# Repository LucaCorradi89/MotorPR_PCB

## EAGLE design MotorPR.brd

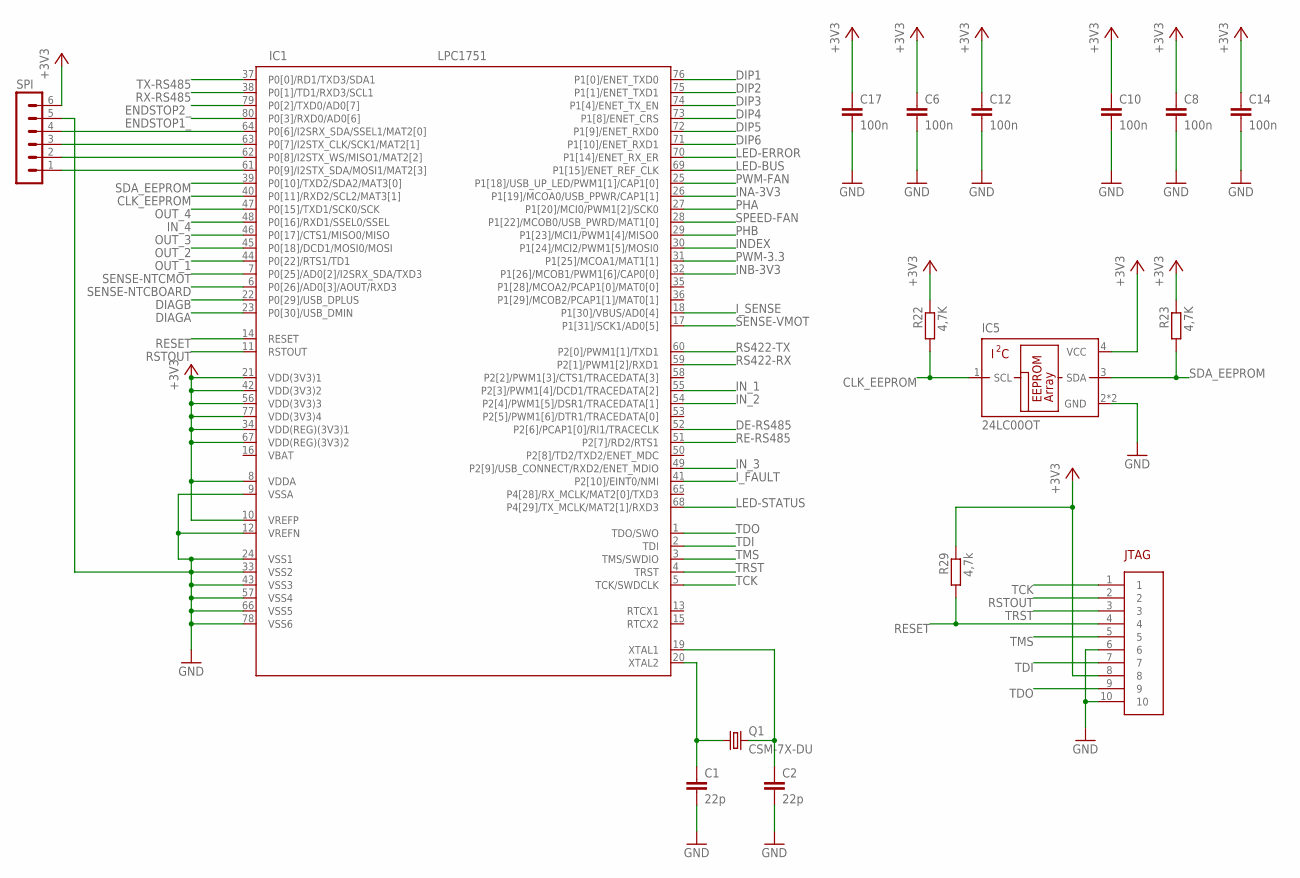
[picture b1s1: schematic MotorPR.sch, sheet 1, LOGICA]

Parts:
C1, C2: 22p; C0805
C6, C8, C10, C12, C14, C17: 100n; C0805
IC1: LPC1751; LQFP80-12X12
IC5: 24LC00OT; SOT23-5L
JTAG: MOLEX-52808-1070
Q1: CSM-7X-DU
R22, R23: 4,7K; R0805W
R29: 4,7k; R0805W
SPI: MA06-1

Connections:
+3V3: C6.1, C8.1, C10.1, C12.1, C14.1, C17.1, IC1.8 (VDDA), IC1.10 (VREFP), IC1.21 (VDD(3V3)1), IC1.34 (VDD(REG)(3V3)1), IC1.42 (VDD(3V3)2), IC1.56 (VDD(3V3)3), IC1.67 (VDD(REG)(3V3)2), IC1.77 (VDD(3V3)4), IC5.4 (VCC), JTAG.8, R22.1, R23.1, R29.1, SPI.6; also elsewhere on the board
CLK_EEPROM: IC1.40 (P0[11]/RXD2/SCL2/MAT3[1]), IC5.1 (SCL), R22.2
DE-RS485: IC1.52 (P2[6]/PCAP1[0]/RI1/TRACECLK); also elsewhere on the board
DIAGA: IC1.23 (P0[30]/USB_DMIN); also elsewhere on the board
DIAGB: IC1.22 (P0[29]/USB_DPLUS); also elsewhere on the board
DIP1: IC1.76 (P1[0]/ENET_TXD0); also elsewhere on the board
DIP2: IC1.75 (P1[1]/ENET_TXD1); also elsewhere on the board
DIP3: IC1.74 (P1[4]/ENET_TX_EN); also elsewhere on the board
DIP4: IC1.73 (P1[8]/ENET_CRS); also elsewhere on the board
DIP5: IC1.72 (P1[9]/ENET_RXD0); also elsewhere on the board
DIP6: IC1.71 (P1[10]/ENET_RXD1); also elsewhere on the board
ENDSTOP1_: IC1.80 (P0[3]/RXD0/AD0[6]); also elsewhere on the board
ENDSTOP2_: IC1.79 (P0[2]/TXD0/AD0[7]); also elsewhere on the board
GND: C1.2, C2.2, C6.2, C8.2, C10.2, C12.2, C14.2, C17.2, IC1.9 (VSSA), IC1.12 (VREFN), IC1.24 (VSS1), IC1.33 (VSS2), IC1.43 (VSS3), IC1.57 (VSS4), IC1.66 (VSS5), IC1.78 (VSS6), IC5.2 (GND), IC5.5 (GND), JTAG.6, JTAG.10, SPI.5; also elsewhere on the board
INA-3V3: IC1.26 (P1[19]/MCOA0/USB_PPWR/CAP1[1]); also elsewhere on the board
INB-3V3: IC1.32 (P1[26]/MCOB1/PWM1[6]/CAP0[0]); also elsewhere on the board
INDEX: IC1.30 (P1[24]/MCI2/PWM1[5]/MOSI0); also elsewhere on the board
IN_1: IC1.55 (P2[3]/PWM1[4]/DCD1/TRACEDATA[2]); also elsewhere on the board
IN_2: IC1.54 (P2[4]/PWM1[5]/DSR1/TRACEDATA[1]); also elsewhere on the board
IN_3: IC1.49 (P2[9]/USB_CONNECT/RXD2/ENET_MDIO); also elsewhere on the board
IN_4: IC1.48 (P0[16]/RXD1/SSEL0/SSEL); also elsewhere on the board
I_FAULT: IC1.41 (P2[10]/EINT0/NMI); also elsewhere on the board
I_SENSE: IC1.18 (P1[30]/VBUS/AD0[4]); also elsewhere on the board
LED-BUS: IC1.69 (P1[15]/ENET_REF_CLK); also elsewhere on the board
LED-ERROR: IC1.70 (P1[14]/ENET_RX_ER); also elsewhere on the board
LED-STATUS: IC1.68 (P4[29]/TX_MCLK/MAT2[1]/RXD3); also elsewhere on the board
unnamed: C2.1, IC1.19 (XTAL1), Q1.2
unnamed: IC1.61 (P0[9]/I2STX_SDA/MOSI1/MAT2[3]), SPI.1
unnamed: C1.1, IC1.20 (XTAL2), Q1.1
unnamed: IC1.62 (P0[8]/I2STX_WS/MISO1/MAT2[2]), SPI.2
unnamed: IC1.63 (P0[7]/I2STX_CLK/SCK1/MAT2[1]), SPI.3
unnamed: IC1.64 (P0[6]/I2SRX_SDA/SSEL1/MAT2[0]), SPI.4
OUT_1: IC1.44 (P0[22]/RTS1/TD1); also elsewhere on the board
OUT_2: IC1.45 (P0[18]/DCD1/MOSI0/MOSI); also elsewhere on the board
OUT_3: IC1.46 (P0[17]/CTS1/MISO0/MISO); also elsewhere on the board
OUT_4: IC1.47 (P0[15]/TXD1/SCK0/SCK); also elsewhere on the board
PHA: IC1.27 (P1[20]/MCI0/PWM1[2]/SCK0); also elsewhere on the board
PHB: IC1.29 (P1[23]/MCI1/PWM1[4]/MISO0); also elsewhere on the board
PWM-3.3: IC1.31 (P1[25]/MCOA1/MAT1[1]); also elsewhere on the board
PWM-FAN: IC1.25 (P1[18]/USB_UP_LED/PWM1[1]/CAP1[0]); also elsewhere on the board
RE-RS485: IC1.51 (P2[7]/RD2/RTS1); also elsewhere on the board
RESET: IC1.14 (RESET), JTAG.4, R29.2
RS422-RX: IC1.59 (P2[1]/PWM1[2]/RXD1); also elsewhere on the board
RS422-TX: IC1.60 (P2[0]/PWM1[1]/TXD1); also elsewhere on the board
RSTOUT: IC1.11 (RSTOUT), JTAG.2
RX-RS485: IC1.38 (P0[1]/TD1/RXD3/SCL1); also elsewhere on the board
SDA_EEPROM: IC1.39 (P0[10]/TXD2/SDA2/MAT3[0]), IC5.3 (SDA), R23.2
SENSE-NTCBOARD: IC1.6 (P0[26]/AD0[3]/AOUT/RXD3); also elsewhere on the board
SENSE-NTCMOT: IC1.7 (P0[25]/AD0[2]/I2SRX_SDA/TXD3); also elsewhere on the board
SENSE-VMOT: IC1.17 (P1[31]/SCK1/AD0[5]); also elsewhere on the board
SPEED-FAN: IC1.28 (P1[22]/MCOB0/USB_PWRD/MAT1[0]); also elsewhere on the board
TCK: IC1.5 (TCK/SWDCLK), JTAG.1
TDI: IC1.2 (TDI), JTAG.7
TDO: IC1.1 (TDO/SWO), JTAG.9
TMS: IC1.3 (TMS/SWDIO), JTAG.5
TRST: IC1.4 (TRST), JTAG.3
TX-RS485: IC1.37 (P0[0]/RD1/TXD3/SDA1); also elsewhere on the board
VBAT: IC1.16 (VBAT)

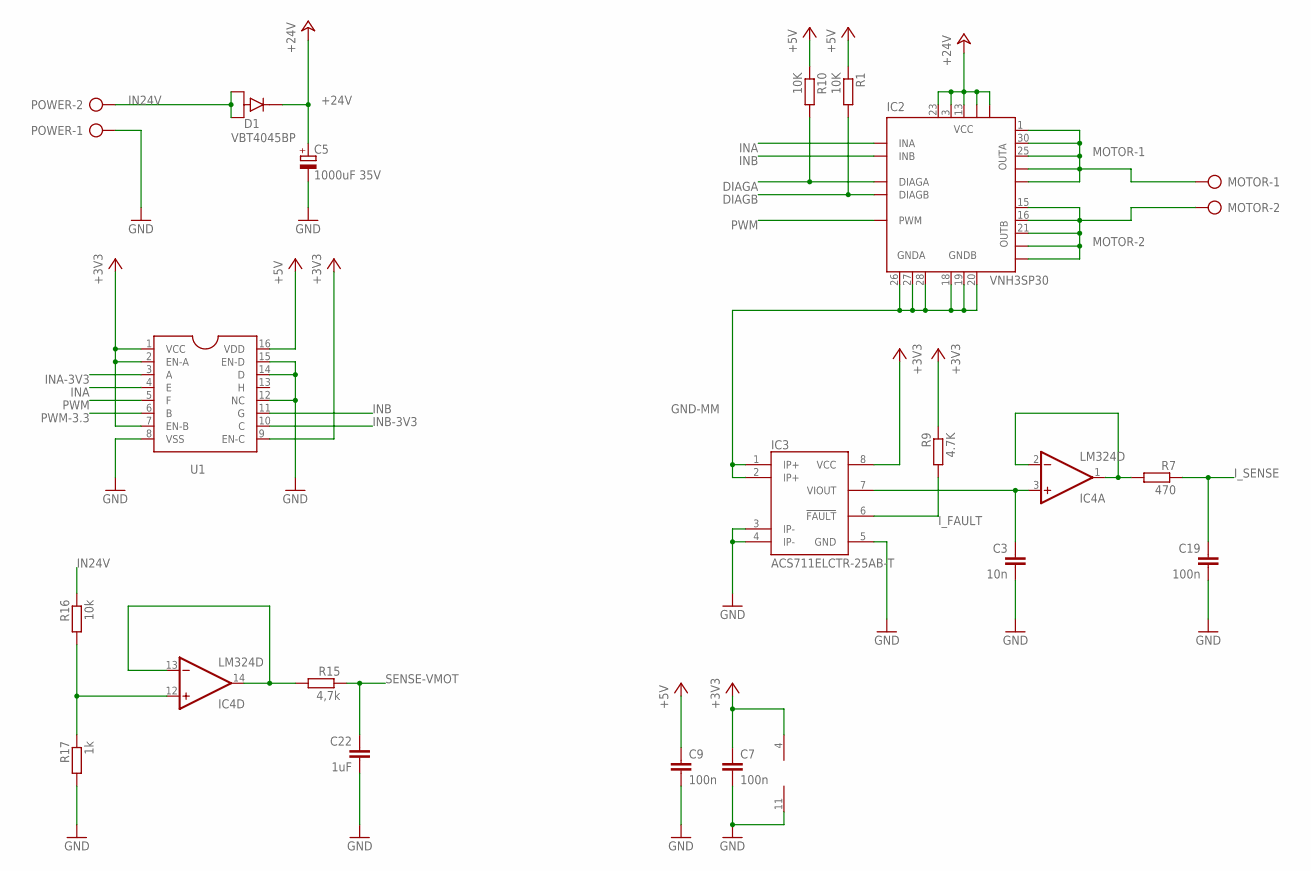
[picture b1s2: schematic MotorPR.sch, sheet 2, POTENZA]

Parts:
C3: 10n; C0805
C5: 1000uF 35V; E7,5-18
C7, C9, C19: 100n; C0805
C22: 1uF; C0805
D1: VBT4045BP; TO-263AB
IC2: VNH3SP30; MULTIPOWERSO-30
IC3: ACS711ELCTR-25AB-T; SO08
IC4: LM324D; SO14
MOTOR: AK300/2
POWER: AK300/2
R1, R10: 10K; R0805W
R7: 470; R0805W
R9: 4.7K; R0805W
R15: 4,7k; R0805W
R16: 10k; M1206
R17: 1k; M1206
U1: CD40109B; PW-PDSO-G16

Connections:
+3V3: C7.1, IC3.8 (VCC), IC4.4 (V+), R9.1, U1.1 (VCC), U1.2 (EN-A), U1.7 (EN-B), U1.9 (EN-C); also elsewhere on the board
+5V: C9.1, R1.1, R10.1, U1.16 (VDD); also elsewhere on the board
+24V: C5.+, D1.K, IC2.3 (VCC), IC2.13 (VCC), IC2.23 (VCC), IC2.VCC, IC2.VCC@1 (VCC)
DIAGA: IC2.6 (DIAGA), R10.2; also elsewhere on the board
DIAGB: IC2.10 (DIAGB), R1.2; also elsewhere on the board
GND: C3.2, C5.-, C7.2, C9.2, C19.2, C22.2, IC3.3 (IP-), IC3.4 (IP-), IC3.5 (GND), IC4.11 (V-), POWER.1, R17.2, U1.8 (VSS), U1.12 (NC), U1.14 (D), U1.15 (EN-D); also elsewhere on the board
GND-MM: IC2.18 (GNDB), IC2.19 (GNDB), IC2.20 (GNDB), IC2.26 (GNDA), IC2.27 (GNDA), IC2.28 (GNDA), IC3.1 (IP+), IC3.2 (IP+)
IN24V: D1.A1, D1.A2, POWER.2, R16.1; also elsewhere on the board
INA: IC2.5 (INA), U1.4 (E)
INA-3V3: U1.3 (A); also elsewhere on the board
INB: IC2.11 (INB), U1.11 (G)
INB-3V3: U1.10 (C); also elsewhere on the board
I_FAULT: IC3.6 (!FAULT!), R9.2; also elsewhere on the board
I_SENSE: C19.1, R7.1; also elsewhere on the board
MOTOR-1: IC2.1 (OUTA), IC2.25 (OUTA), IC2.30 (OUTA), IC2.OUTA, IC2.OUTA@1 (OUTA), MOTOR.1
MOTOR-2: IC2.15 (OUTB), IC2.16 (OUTB), IC2.21 (OUTB), IC2.OUTB, IC2.OUTB@1 (OUTB), MOTOR.2
unnamed: C3.1, IC3.7 (VIOUT), IC4.3 (+IN)
unnamed: IC4.13 (-IN), IC4.14 (OUT), R15.2
unnamed: IC4.1 (OUT), IC4.2 (-IN), R7.2
unnamed: IC4.12 (+IN), R16.2, R17.1
PWM: IC2.8 (PWM), U1.5 (F)
PWM-3.3: U1.6 (B); also elsewhere on the board
SENSE-VMOT: C22.1, R15.1; also elsewhere on the board

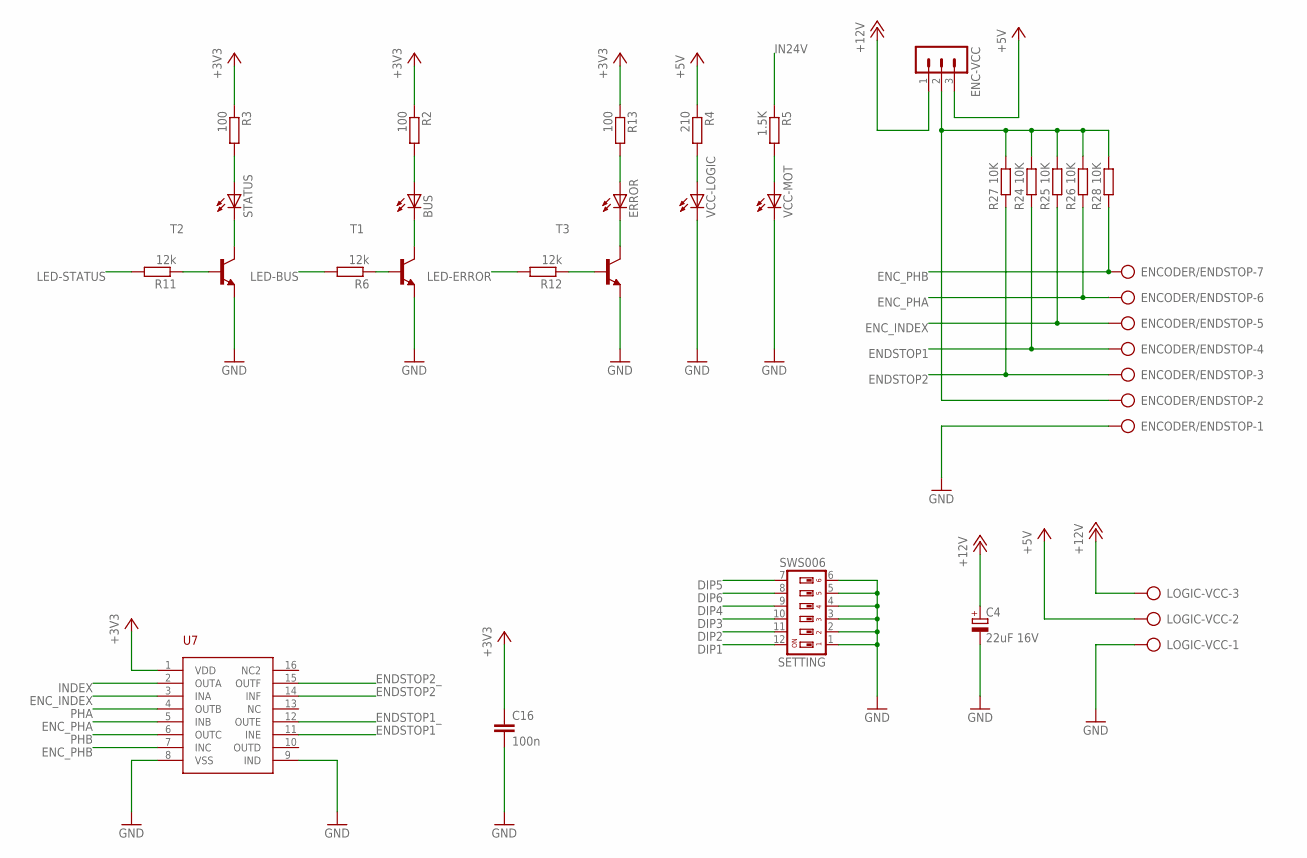
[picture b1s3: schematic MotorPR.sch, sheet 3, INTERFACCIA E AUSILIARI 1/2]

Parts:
BUS: LEDCHIPLED_1206; CHIPLED_1206
C4: 22uF 16V; 153CLV-0605
C16: 100n; C0805
ENC-VCC: MA03-1
ENCODER/ENDSTOP: AK300/7
ERROR: LEDCHIPLED_1206; CHIPLED_1206
LOGIC-VCC: AK300/3
R2, R3, R13: 100; R0805W
R4: 210; R0805W
R5: 1.5K; R0805W
R6, R11, R12: 12k; R0805W
R24, R25, R26, R27, R28: 10K; R0805W
SETTING: SWS006; DIP6-SMD
STATUS: LEDCHIPLED_1206; CHIPLED_1206
T1, T2, T3: BC808-NPN-SOT23-BEC; SOT23-BEC
U7: MC14050B; PDSO-G16
VCC-LOGIC: LEDCHIPLED_1206; CHIPLED_1206
VCC-MOT: LEDCHIPLED_1206; CHIPLED_1206

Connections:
+3V3: C16.1, R2.1, R3.1, R13.1, U7.1 (VDD); also elsewhere on the board
+5V: ENC-VCC.3, LOGIC-VCC.2, R4.1; also elsewhere on the board
+12V: C4.+, ENC-VCC.1, LOGIC-VCC.3; also elsewhere on the board
DIP1: SETTING.12; also elsewhere on the board
DIP2: SETTING.11; also elsewhere on the board
DIP3: SETTING.10; also elsewhere on the board
DIP4: SETTING.9; also elsewhere on the board
DIP5: SETTING.7; also elsewhere on the board
DIP6: SETTING.8; also elsewhere on the board
ENC_INDEX: ENCODER/ENDSTOP.5, R25.2, U7.3 (INA)
ENC_PHA: ENCODER/ENDSTOP.6, R26.2, U7.5 (INB)
ENC_PHB: ENCODER/ENDSTOP.7, R28.2, U7.7 (INC)
ENDSTOP1: ENCODER/ENDSTOP.4, R24.2, U7.11 (INE)
ENDSTOP1_: U7.12 (OUTE); also elsewhere on the board
ENDSTOP2: ENCODER/ENDSTOP.3, R27.2, U7.14 (INF)
ENDSTOP2_: U7.15 (OUTF); also elsewhere on the board
GND: C4.-, C16.2, ENCODER/ENDSTOP.1, LOGIC-VCC.1, SETTING.1, SETTING.2, SETTING.3, SETTING.4, SETTING.5, SETTING.6, T1.E, T2.E, T3.E, U7.8 (VSS), U7.9 (IND), VCC-LOGIC.C, VCC-MOT.C; also elsewhere on the board
IN24V: R5.1; also elsewhere on the board
INDEX: U7.2 (OUTA); also elsewhere on the board
LED-BUS: R6.2; also elsewhere on the board
LED-ERROR: R12.2; also elsewhere on the board
LED-STATUS: R11.2; also elsewhere on the board
unnamed: R6.1, T1.B
unnamed: R11.1, T2.B
unnamed: R12.1, T3.B
unnamed: R5.2, VCC-MOT.A
unnamed: R4.2, VCC-LOGIC.A
unnamed: BUS.C, T1.C
unnamed: BUS.A, R2.2
unnamed: ERROR.A, R13.2
unnamed: ERROR.C, T3.C
unnamed: STATUS.C, T2.C
unnamed: R3.2, STATUS.A
unnamed: ENC-VCC.2, ENCODER/ENDSTOP.2, R24.1, R25.1, R26.1, R27.1, R28.1
PHA: U7.4 (OUTB); also elsewhere on the board
PHB: U7.6 (OUTC); also elsewhere on the board

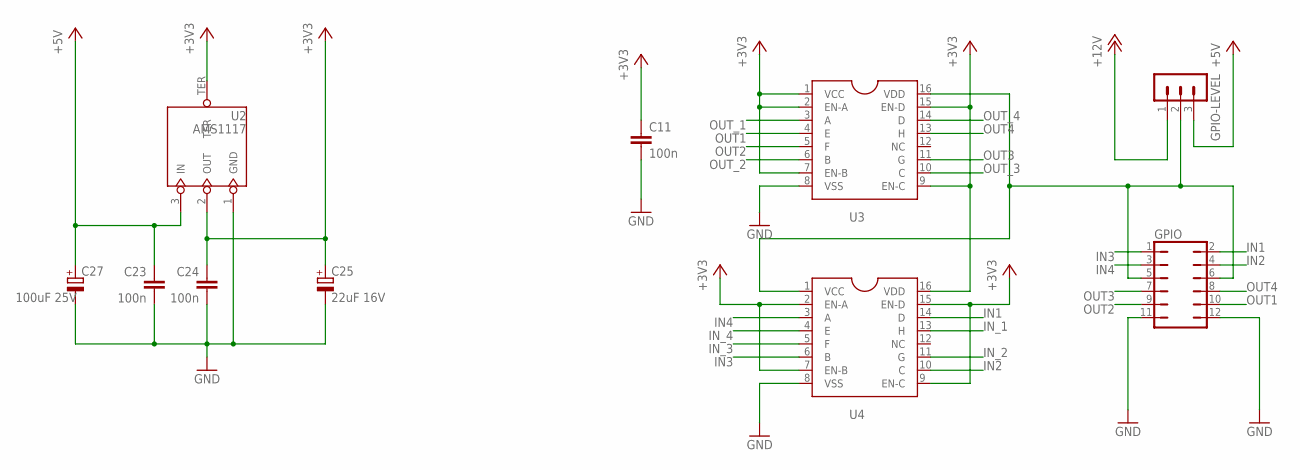
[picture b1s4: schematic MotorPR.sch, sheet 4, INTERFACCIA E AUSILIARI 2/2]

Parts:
C11, C23, C24: 100n; C0805
C25: 22uF 16V; 153CLV-0605
C27: 100uF 25V; 153CLV-0807
GPIO: JP6Q
GPIO-LEVEL: MA03-1
U2: AMS1117; SOT-223
U3, U4: CD40109B; PW-PDSO-G16

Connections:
+3V3: C11.1, C24.1, C25.+, U2.2 (OUT), U2.TER, U3.1 (VCC), U3.2 (EN-A), U3.7 (EN-B), U3.9 (EN-C), U3.15 (EN-D), U4.2 (EN-A), U4.7 (EN-B), U4.9 (EN-C), U4.15 (EN-D), U4.16 (VDD); also elsewhere on the board
+5V: C23.1, C27.+, GPIO-LEVEL.3, U2.3 (IN); also elsewhere on the board
+12V: GPIO-LEVEL.1; also elsewhere on the board
GND: C11.2, C23.2, C24.2, C25.-, C27.-, GPIO.11, GPIO.12, U2.1 (GND), U3.8 (VSS), U4.8 (VSS); also elsewhere on the board
IN1: GPIO.2, U4.14 (D)
IN2: GPIO.4, U4.10 (C)
IN3: GPIO.1, U4.6 (B)
IN4: GPIO.3, U4.3 (A)
IN_1: U4.13 (H); also elsewhere on the board
IN_2: U4.11 (G); also elsewhere on the board
IN_3: U4.5 (F); also elsewhere on the board
IN_4: U4.4 (E); also elsewhere on the board
unnamed: GPIO.5, GPIO.6, GPIO-LEVEL.2, U3.16 (VDD), U4.1 (VCC)
OUT1: GPIO.10, U3.4 (E)
OUT2: GPIO.9, U3.5 (F)
OUT3: GPIO.7, U3.11 (G)
OUT4: GPIO.8, U3.13 (H)
OUT_1: U3.3 (A); also elsewhere on the board
OUT_2: U3.6 (B); also elsewhere on the board
OUT_3: U3.10 (C); also elsewhere on the board
OUT_4: U3.14 (D); also elsewhere on the board

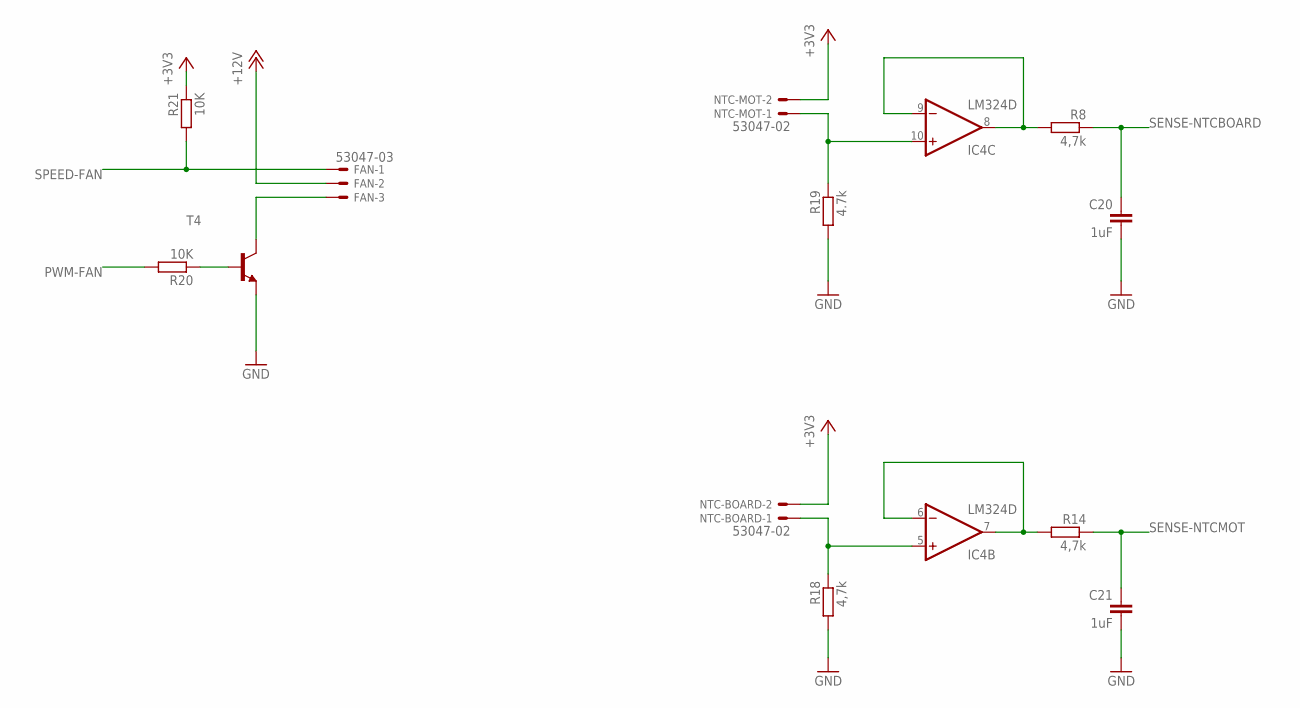
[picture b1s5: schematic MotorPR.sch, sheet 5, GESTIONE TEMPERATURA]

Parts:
C20, C21: 1uF; C0805
FAN: 53047-03
IC4: LM324D; SO14
NTC-BOARD: 53047-02
NTC-MOT: 53047-02; MPN 53047-0210
R8, R14: 4,7k; R0805W
R18: 4,7k; M1206
R19: 4.7k; M1206
R20, R21: 10K; R0805W
T4: BC808-NPN-SOT23-BEC; SOT23-BEC

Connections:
+3V3: NTC-BOARD.2, NTC-MOT.2, R21.1; also elsewhere on the board
+12V: FAN.2; also elsewhere on the board
GND: C20.2, C21.2, R18.2, R19.2, T4.E; also elsewhere on the board
unnamed: IC4.8 (OUT), IC4.9 (-IN), R8.2
unnamed: IC4.6 (-IN), IC4.7 (OUT), R14.2
unnamed: IC4.5 (+IN), NTC-BOARD.1, R18.1
unnamed: IC4.10 (+IN), NTC-MOT.1, R19.1
unnamed: R20.1, T4.B
unnamed: FAN.3, T4.C
PWM-FAN: R20.2; also elsewhere on the board
SENSE-NTCBOARD: C20.1, R8.1; also elsewhere on the board
SENSE-NTCMOT: C21.1, R14.1; also elsewhere on the board
SPEED-FAN: FAN.1, R21.2; also elsewhere on the board

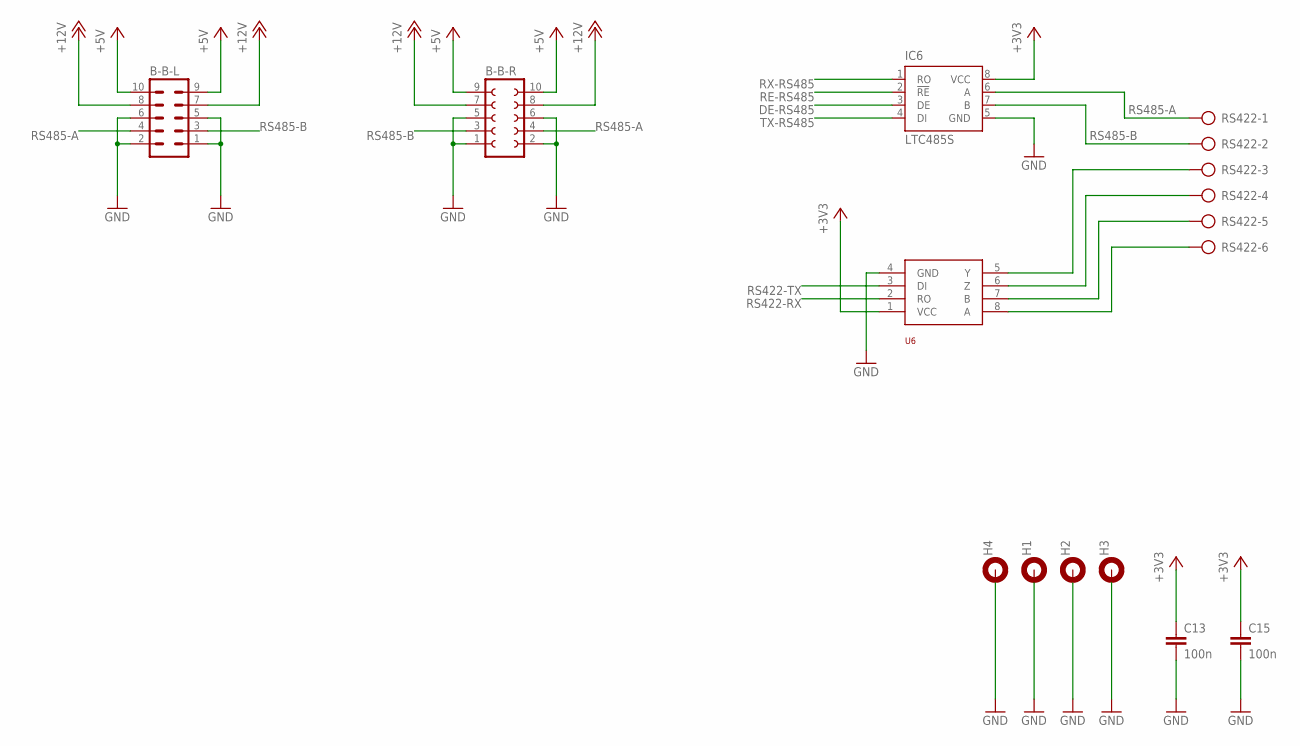
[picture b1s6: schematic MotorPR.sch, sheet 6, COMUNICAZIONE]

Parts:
B-B-L: MA05-2
B-B-R: FE05-2W
C13, C15: 100n; C0805
H1, H2, H3, H4: MOUNT-PAD-ROUND3.0; 3,0-PAD
IC6: LTC485S; SOIC8
RS422: AK300/6
U6: ISL83490IBZ; R-PDSO-G8

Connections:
+3V3: C13.1, C15.1, IC6.8 (VCC), U6.1 (VCC); also elsewhere on the board
+5V: B-B-L.9, B-B-L.10, B-B-R.9, B-B-R.10; also elsewhere on the board
+12V: B-B-L.7, B-B-L.8, B-B-R.7, B-B-R.8; also elsewhere on the board
DE-RS485: IC6.3 (DE); also elsewhere on the board
GND: B-B-L.1, B-B-L.2, B-B-L.5, B-B-L.6, B-B-R.1, B-B-R.2, B-B-R.5, B-B-R.6, C13.2, C15.2, H1.B3,0, H2.B3,0, H3.B3,0, H4.B3,0, IC6.5 (GND), U6.4 (GND); also elsewhere on the board
unnamed: RS422.3, U6.5 (Y)
unnamed: RS422.4, U6.6 (Z)
unnamed: RS422.5, U6.7 (B)
unnamed: RS422.6, U6.8 (A)
RE-RS485: IC6.2 (!RE); also elsewhere on the board
RS422-RX: U6.2 (RO); also elsewhere on the board
RS422-TX: U6.3 (DI); also elsewhere on the board
RS485-A: B-B-L.4, B-B-R.4, IC6.6 (A), RS422.1
RS485-B: B-B-L.3, B-B-R.3, IC6.7 (B), RS422.2
RX-RS485: IC6.1 (RO); also elsewhere on the board
TX-RS485: IC6.4 (DI); also elsewhere on the board

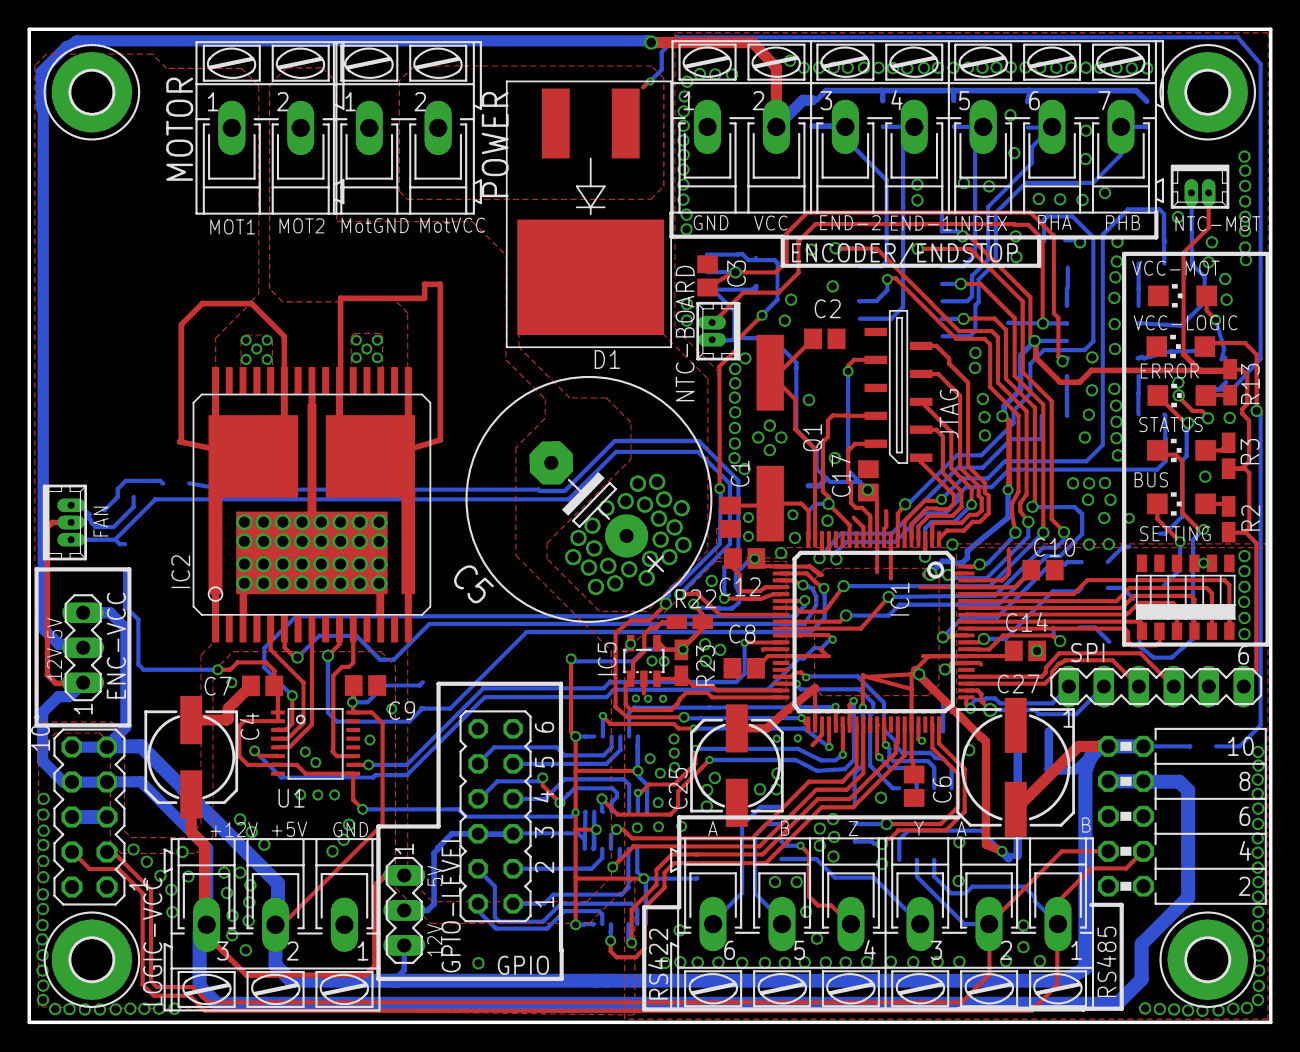
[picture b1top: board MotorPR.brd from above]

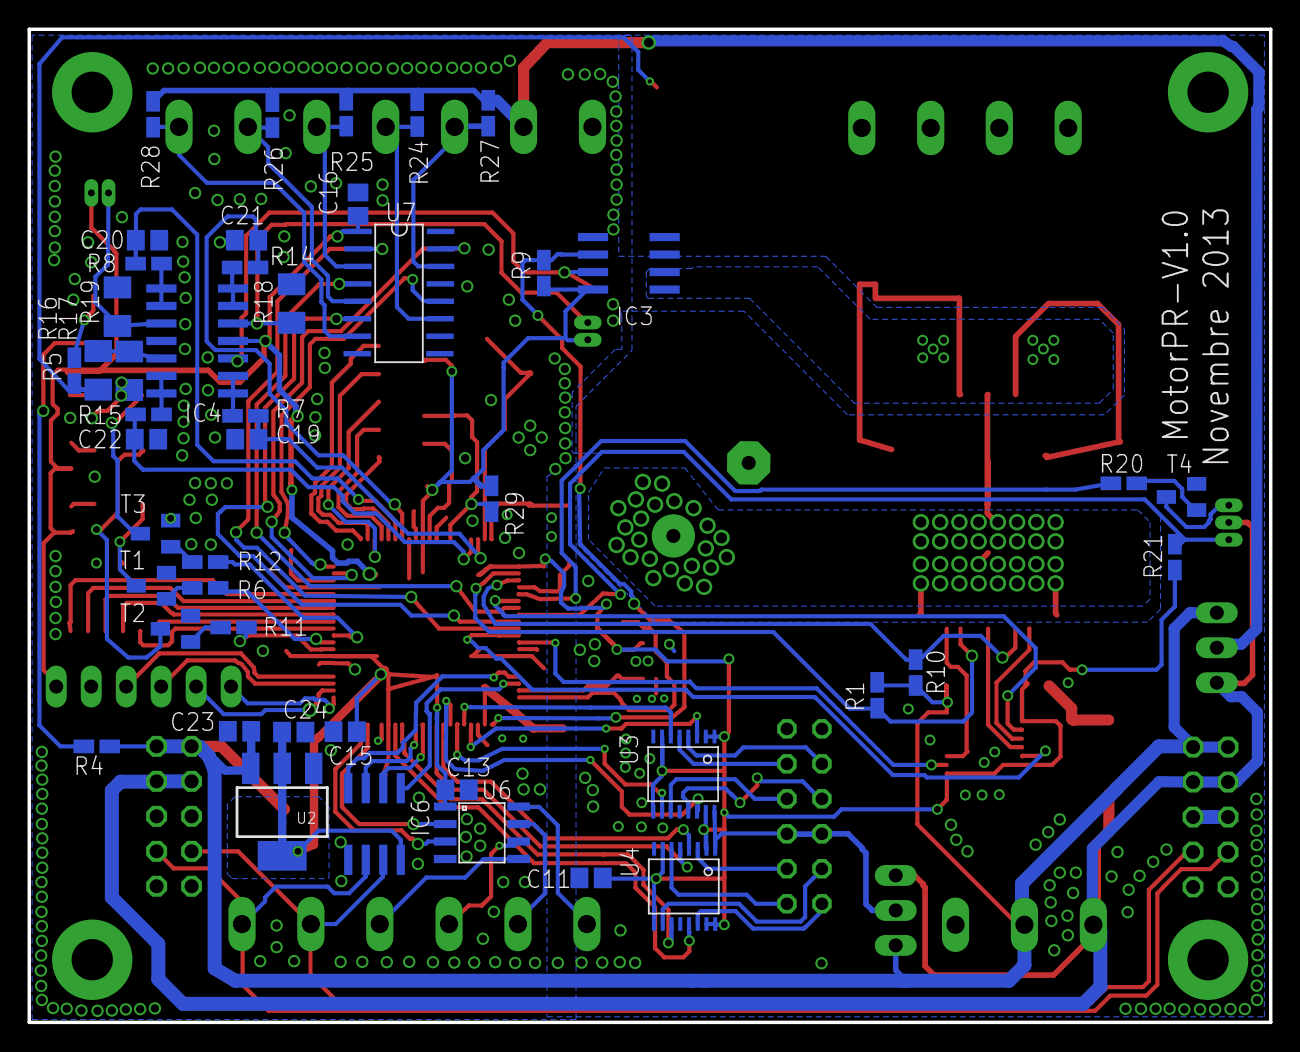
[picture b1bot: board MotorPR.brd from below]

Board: 2 copper layers, 90.1 x 72.1 mm, 97 parts (46 on the bottom side), 109 nets.

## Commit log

2021-03-21 PRIMO COMMIT
